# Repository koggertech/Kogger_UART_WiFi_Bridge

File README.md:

# Kogger Wi‑Fi Bridge

Firmware for a small ESP32‑C3‑MINI‑1U board that puts serial devices on Wi‑Fi.

- **Frame‑aware UART ↔ Wi‑Fi relay.** Two UART lines, each mapped to its own UDP port or TCP client.
  Traffic travels as whole protocol frames (Kogger SBP KP1/KP2, u‑blox UBX, MAVLink 1/2) packed into
  datagrams of at most 512 bytes. Anything else passes through as raw bytes, in order.
- **Kogger SBP device** (board ID 87) **on either port.** A host that speaks Kogger SBP uses X1 or X2, in either
  role, to configure Wi‑Fi, the relay and the network, to read state and statistics, and to update the firmware;
  everything except firmware updates also works over the network. The module answers discovery (`ID_VERSION` to
  address 0), so KoggerApp finds it without knowing its address, and it reports what it sees on each port: the rates,
  whether a host or devices sit there, the devices heard, the traffic by protocol. The update exchange is
  the one KoggerApp uses for Kogger devices; its file dialog needs `*.ufww` added ([docs/UPDATE.md](docs/UPDATE.md)).
  The Wi‑Fi settings need a host that implements the `ID_WIFI` / `ID_WIFI_NET` contract
  ([docs/SBP_WIFI.md](docs/SBP_WIFI.md)); `host/sbpframe.py` has Python helpers for the frame and for
  most payloads (state, scan, saved networks, radio, role, access point, addresses, lines, clients).
- **Station or access point.** As a station the module joins an existing network: up to 8 saved networks,
  auto‑connect to the strongest one. As an access point it runs its own network with a DHCP server for up
  to 10 clients.
- **IP bridge (optional).** IPv4 packets over SLIP on the serial link, NAT into Wi‑Fi. This is for a Linux
  host without a Wi‑Fi adapter; the daemon is in `host/`.
- **Safe updates.** Two firmware slots, the image is checked before the switch, and an image that does not
  prove itself is rolled back automatically.
- **GODIO boat telemetry.** Line 1 can listen to the controller wire of a GODIO boat and pass on its position,
  heading and supply voltage as MAVLink ([docs/GODIO_F9.md](docs/GODIO_F9.md)).
- **Reproducible build.** The same sources and ESP‑IDF give the same image byte for byte, so a release
  file can be checked by building its tag.

## Example application

HeadUnit is a boat display computer, a Linux board that talks Kogger SBP to the boat's equipment. It has no usable
Wi‑Fi of its own, so the module sits on one of its UARTs at 3 Mbaud and joins the boat's access point. The equipment
on the boat sends Kogger SBP, MAVLink and UBX; the module relays this traffic between the head unit and the boat over
UDP. On the same port the module answers its own SBP address 87 and sends its Wi‑Fi state reports.

In the access‑point role the same board can be the boat‑side end: it bridges a sonar or autopilot
UART to phones and laptops on its own network.

## Key figures (firmware 0.23.0)

| | |
|---|---|
| Module | ESP32‑C3‑MINI‑1U (RISC‑V, 160 MHz, 4 MB flash, U.FL antenna connector) |
| Board | 20 × 30 mm, 4 layers; two JST GH 4‑pin connectors; supply 4.5–24 V on X1 (3.3 V / 1 A step‑down module) |
| Wi‑Fi | 802.11 b/g/n, 2.4 GHz, 20/40 MHz; Espressif LR mode optional; TX power 2–20 dBm in 11 steps |
| Roles | station (default) or access point (open, WPA2, WPA2/WPA3; channels 1–11; up to 10 clients) |
| Serial lines | X1 = UART0, X2 = UART1, equal for control and relay; 9600–5 000 000 baud, 8N1, set for each port; default 921600 on both |
| Relay | per line: off, UDP (fixed peer, last ≤ 4 senders, or broadcast) or TCP client; frames up to 4096 B |
| Control | Kogger SBP: `ID_WIFI` 0x57, `ID_WIFI_NET` 0x58, `ID_WIFI_SURVEY` 0x59, `ID_WIFI_RF` 0x5A, `ID_WIFI_PROFILE` 0x5B and the common device IDs, from any line or the network |
| Antenna swap | the radio switched off over SBP until a timer (needed when asked over the network, up to 600 s), an "on" request or a reboot (0.20) |
| Status LED | lit steadily without a link, a 100 ms flash every 2.1 s with one (0.20) |
| Profiles | every saved setting loaded as one profile: checked whole, saved at once, then a reboot into it; the module reports the profile's name and whether a setting changed since (0.22) |
| Line 1 translator | GODIO F9 telemetry → MAVLink 2 (position, heading, voltage, satellites), listen‑only; a setting (0.21), in this repository's build from 0.23 |
| Update | over SBP, from a wire or (since 0.17) the network; A/B slots of 1.875 MiB; SHA‑256 check; confirmation after 60 s, rollback at 180 s |
| Factory settings | station knowing the network `KoggerBridge` (build options `WB_FACTORY_SSID` / `WB_FACTORY_PASS`), lines relaying to 10.0.0.10:14444 / 14445; BOOT held 5 s resets the port rates, 10 s every setting |
| Image size | 0.97 MB, 49 % of a slot (0.23.0, UART build); reproducible: no build date, time or path in it |
| Serial throughput | baud / 10 bytes per second each way: 92 KB/s at 921600, 200 KB/s at 2 Mbaud |

The serial line, not Wi‑Fi, is the bottleneck at these rates. Measured figures, test conditions and charts
are in the [datasheet](docs/KoggerWiFi_datasheet.pdf) and in [docs/DESIGN.md](docs/DESIGN.md).

## Documentation

| Document | Contents |
|---|---|
| [docs/HARDWARE.md](docs/HARDWARE.md) | board, connectors, power, wiring, flashing without auto‑reset |
| [docs/FLASHER.md](docs/FLASHER.md) | Windows flasher: firmware into a module in the bootloader, one window, no tools to install |
| [hardware/](hardware/) | KiCad project of the board, schematic PDF, Gerbers, BOM, pick‑and‑place |
| [docs/SBP_WIFI.md](docs/SBP_WIFI.md) | Kogger SBP contract: frame, common IDs, `ID_WIFI` 0x57, `ID_WIFI_NET` 0x58, `ID_WIFI_SURVEY` 0x59, `ID_WIFI_RF` 0x5A, `ID_WIFI_PROFILE` 0x5B |
| [docs/NETWORK.md](docs/NETWORK.md) | station / access point, AP settings, address and DHCP, UART lines and their ports |
| [docs/RELAY.md](docs/RELAY.md) | frame‑aware relay: framing, packing, buffers, back‑pressure, statistics |
| [docs/UPDATE.md](docs/UPDATE.md) | firmware update over SBP: procedure, safety argument, test log |
| [docs/GODIO_F9.md](docs/GODIO_F9.md) | line 1 on a GODIO boat's telemetry wire: wiring, F9 frames, the MAVLink sent, the boat's profile |
| [docs/PROTOCOL.md](docs/PROTOCOL.md) | IP bridge: SLIP framing, text commands, host daemon |
| [docs/PARAMETERS.md](docs/PARAMETERS.md) | every setting with default and range, build options, timing constants, buffers |
| [docs/DESIGN.md](docs/DESIGN.md) | architecture, tasks, memory, ESP‑IDF pitfalls, measurements, open issues |
| [docs/BUILD_AND_TEST.md](docs/BUILD_AND_TEST.md) | build, flash, PC tests, bench tools, host install |
| [docs/KoggerWiFi_datasheet.pdf](docs/KoggerWiFi_datasheet.pdf) | datasheet: summary, parameters and charts |
| [SECURITY.md](SECURITY.md) | security model and what to change before deployment |
| [CHANGELOG.md](CHANGELOG.md) | release history and verification status |

## Repository layout

| Directory | Contents |
|---|---|
| `firmware/` | ESP‑IDF project (C) |
| `host/` | Linux daemon for the IP bridge, CLI client, udev/systemd/NetworkManager files; Python mirrors of the wire formats |
| `tests/` | PC tests: the Python mirrors against the firmware's portable C, compiled on the PC, byte for byte |
| `tools/` | bench tools: flashing, SBP/relay/ping checks, update and packaging, charts and datasheet; `gps_sniffer/`, an identifier of unknown serial lines |
| `profiles/` | module profiles for `tools/profile.py`: a GODIO boat |
| `hardware/` | KiCad 10 project of the reference board and its fabrication outputs |
| `docs/` | documentation, charts, datasheet |
| `LICENSES/` | license notices of included third‑party material (MAVLink generated code) |

## Quick start

Just to put the firmware on a board: download `KoggerWiFiFlasher_EN.exe` and `KoggerWiFi_X.Y.Z.ufww` from the
[releases](https://github.com/koggertech/Kogger_UART_WiFi_Bridge/releases) and follow [docs/FLASHER.md](docs/FLASHER.md).

To build:

```
python tests/test_all.py                       # PC tests, no hardware: "... checks, 0 failed"
python tests/test_f9.py                        # the GODIO F9 translator, the same way
cd firmware
idf.py -B build-uart -D SDKCONFIG=build-uart/sdkconfig -D "SDKCONFIG_DEFAULTS=sdkconfig.defaults;sdkconfig.defaults.uart" build
```

Flashing, the native‑USB variant and the bench checks are described in
[docs/BUILD_AND_TEST.md](docs/BUILD_AND_TEST.md). Tested with ESP‑IDF v5.5.5.

## Status

- **Verified on hardware (0.1–0.18):**
  - SBP device checks;
  - baud rates 9600 to 2 Mbaud on a bench adapter, 2/3/4 Mbaud on a head unit's UART;
  - IP bridge through NAT;
  - station auto‑connect;
  - firmware update, recovery from a lost chunk, a corrupted image refused;
  - relay to a boat network over UDP;
  - 0.11.0 installed on a head unit's module over SBP at 3 Mbaud (7/7 checks), all settings kept;
  - 0.12.0 on a bench module: the port rules (29/29 checks in both roles), the SBP device checks (38/38);
  - 0.12.0 on the head unit's module (7/7); a sonar on the access point's X2 seen on the head unit over an LR‑only
    module‑to‑module link;
  - 0.13.0 on a bench module: both BOOT resets (5 s: only the port rates; 10 s: factory settings), the factory station
    lines, a module set up under an earlier firmware keeping its X2 rate and access point after the update, both ports
    accepting 5 000 000 baud;
  - 0.13.0 and 0.14.0 on the head unit's module (7/7 each), every saved setting read before and compared after
    (`tools/module_state.py`);
  - 0.14.0: 60 requests at once all answered (58 on 0.13), a mixed burst of ten request types answered in full;
  - 0.15.0: a port rate set through that very port saved at once and kept across a reboot; the BOOT 5 s press
    restoring 921600 on both ports with every other setting kept;
  - 0.16.0: a channel survey in the station role - 11 channels swept, the pages, the flags and the refusals
    (`tools/bench_survey.py`), with the Wi-Fi link back afterwards;
  - 0.18.0: the first firmware update over the air - an access-point module updated through a head unit's relay
    (7/7, every setting kept); the link rate on both ends of a b/g/n link, 11n MCS7 with short guard interval both
    ways (`tools/bench_linkrate.py`); an image that could not be confirmed over a busy LR link rolled back to the
    previous one at the next power-on;
  - 0.19.0: both modules updated, one over its UART and one over the air (7/7 each, every setting kept); the LR
    rate field calibrated by frame timing: code 0x1A is 500 kbit/s (bound 372-380 kbit/s in 6 of 6 windows).
- **Not yet verified on hardware:** the timing bound's control on 802.11n frames (none were timed: they came
  aggregated); the channel survey in the access-point role; data at 5 Mbaud (the bench adapter stops at 2 Mbaud); the kept station lines of a
  module updated from 0.12; two factory modules relaying to each other; the 0.11 transmit fix under a saturated 921600 port; an abandoned transfer; a host on X2; the native USB variant; the IP bridge daemon on a Linux host; LR range and throughput over distance.

The status of each release is in [CHANGELOG.md](CHANGELOG.md).

## License

MIT, © 2026 KOGGER LLC, <https://kogger.tech>. See [LICENSE](LICENSE). Third‑party notices: [THIRD_PARTY.md](THIRD_PARTY.md).

The KOGGER logo on the bottom silkscreen of the board is not licensed under the MIT License. The fab zip in
`hardware/outputs` includes it: before making boards that KOGGER LLC does not supply, delete the logo from B.SilkS
and regenerate the outputs with `tools/make_hw_outputs.py`.

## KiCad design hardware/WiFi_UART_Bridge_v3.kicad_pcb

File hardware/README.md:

# Hardware: Wi‑Fi UART bridge board v3

KiCad 10 project of the reference board, the board that was manufactured and is in use. Every drill hole
and every solder‑paste opening of this board matches the fabrication files the board was made from (checked, see
below).

| File | Contents |
|---|---|
| `WiFi_UART_Bridge_v3.kicad_pro` | project (open this in KiCad 10 or later) |
| `WiFi_UART_Bridge_v3.kicad_sch` | schematic, one A4 sheet |
| `WiFi_UART_Bridge_v3.kicad_pcb` | board: 20 × 30 mm, 4 layers |
| `WiFi_UART_Bridge.kicad_sym`, `WiFi_UART_Bridge.pretty/` | project symbol and footprint libraries (`sym-lib-table`, `fp-lib-table`) |
| `3d/` | plain box bodies for renders (module, switch, 4 A diodes); other parts use KiCad library models |
| `outputs/WiFi_UART_Bridge_v3_schematic.pdf` | schematic |
| `outputs/WiFi_UART_Bridge_v3_fab.zip` | Gerbers, Excellon drill, drill map, Gerber job file, pick‑and‑place, BOM |
| `outputs/WiFi_UART_Bridge_v3_bom.csv`, `_pos.csv` | BOM and pick‑and‑place (top side, mm, origin at the lower‑left board corner) |

The outputs are generated by `python tools/make_hw_outputs.py` (needs `kicad-cli` of KiCad 10).

## Board

| | |
|---|---|
| Size | 20 × 30 mm, a 2 mm wide, 4 mm deep notch with a rounded end between the two connectors |
| PCB | 4 layers, FR4 1.2 mm, 18 µm copper, ENIG finish, green solder mask, white silkscreen |
| Stackup in the file | nominal: 0.2 mm prepreg, 0.708 mm core, 0.2 mm prepreg; use the fab's standard 1.2 mm 4‑layer stackup |
| Layers | F.Cu: signals and GND pour; In1.Cu: GND; In2.Cu: VCC, +3.3 V and UART routing plus a GND pour; B.Cu: GND pour and the test pads |
| Design rules | track 0.2 mm min, clearance 0.2 mm, vias 0.7/0.3 mm (82), copper to edge 0.25 mm |
| Components | 37 on the top side; 4 test pads on the bottom |

## Circuit

- **Module U1:** ESP32‑C3‑MINI‑1U with a U.FL connector for an external 2.4 GHz antenna. The EN pin has a 10 kΩ
  pull‑up and 1 µF to GND (power‑on delay). The strapping pins GPIO2, GPIO8 and GPIO9 have 10 kΩ pull‑ups.
  The BOOT button SB1 pulls GPIO9 low.
- **Power:**
  - VCC arrives on X1 pin 4 through the Schottky diode D9 (SDM4A40EP3, reverse‑polarity protection).
  - The step‑down module U2 (TI LMZM23601V3: 4–36 V in, 3.3 V out, up to 1 A per TI) makes +3.3 V.
  - VCC range: 4.5–24 V (rated; not measured on a board). The lower limit is the regulator's 4 V plus the diode
    drop; the upper limit stays below the 25 V rating of the input capacitors C5/C6.
- **X2 pin 4 (VCC_X2):** two 0 Ω links. R8 connects it to VCC. R9 + D8 feed it from +3.3 V through a Schottky
  diode. Both links are fitted in the BOM, so X2 pin 4 carries VCC; with R8 left out it carries about 3 V. Through R8
  the board can also be powered from X2 pin 4, without the reverse‑polarity diode.
- **UART protection:** each line has a series resistor on the connector side, 150 Ω on TX and 1 kΩ on RX. On the
  module side, Schottky diodes (BAS3005B‑02V) clamp each line to GND and to a clamp rail 3.3S. D1 feeds that rail from
  +3.3 V; the 3.3 V Zener D12 and C4 absorb the clamp current, so over‑voltage on a connector does not pump up +3.3 V.
- **LED VD1:** GPIO0 → 1 kΩ → green LED → GND, lit when GPIO0 is high. Since 0.20 the firmware shows the link on it
  ([docs/HARDWARE.md](../docs/HARDWARE.md)).
- **Test pads on the bottom (1.6 mm):** TP1 DM (GPIO18, USB D−), TP2 DP (GPIO19, USB D+), TP3 TX and TP4 RX of line 1
  (GPIO5/GPIO4). The USB pads allow flashing through the C3's USB Serial/JTAG.

| Connector | Pin 1 | Pin 2 | Pin 3 | Pin 4 |
|---|---|---|---|---|
| X1 (line 0) | TX (GPIO21) | RX (GPIO20) | GND | VCC in (through D9) |
| X2 (line 1) | TX (GPIO5) | RX (GPIO4) | GND | VCC_X2 |

X1 and X2 are JST GH 4‑pin headers, 1.25 mm, right angle (SM04B‑GHS‑TB). The mating housing is GHR‑04V‑S.
The bottom silkscreen names the pins.

## How the KiCad project was checked

1. **Board:**
   - footprints in one project library with plain names;
   - courtyards on U1, U2, X1, X2 and SB1 and fab outlines on U2, X1, X2 and SB1; the passives, diodes and LED have
     silkscreen outlines only, the test pads none (the board's DRC does not require courtyards);
   - footprints linked to their schematic symbols by UUID;
   - KiCad library 3D models, aligned by fitting the library footprint's pads onto these pads (residual ≤ 0.1 mm),
     plus three plain boxes;
   - stackup 1.2 mm, 18 µm copper, ENIG, green solder mask, white silkscreen;
   - drill/place origin at the lower‑left corner.
2. **Connectivity:** the schematic netlist and the board partition all 134 pins into the same 32 nets. The only board
   pads without a symbol pin are 14 unconnected NC pads of U1.
3. **Against the fabrication files of the manufactured board:**
   - all 82 drill holes match (≤ 0.0005 mm);
   - all 152 top and 4 bottom solder‑paste openings match in position (≤ 0.0004 mm) and size;
   - in the original pick‑and‑place file 33 of 37 parts match exactly. For D8, D9, X1 and X2 that file gives a body
     centre instead of the footprint origin; their pads are among the matched paste openings.
4. **ERC:** clean. **DRC with schematic parity:** no parity errors, no unconnected items, no clearance errors.
   Remaining items are inherited from the original layout:
   - 1 error: C3 pad 2 has a single thermal spoke into the top GND pour after the zones are refilled;
   - 26 warnings: silkscreen text 0.7 mm high, below KiCad's default minimum of 0.8 mm;
   - 3 warnings: silkscreen over copper.

Changes to the content of the original design, all visible in the files:
- The four bottom test pads were free pads in the original layout. They are now test points TP1–TP4 in the schematic
  and on the board, excluded from the BOM and the pick‑and‑place.
- PWR_FLAG symbols and a "Power flags for ERC" block were added, as KiCad's ERC requires. U2's DNC and PGOOD pins got
  no‑connect marks.
- Part data come from the production BOM: value, manufacturer part number, manufacturer. Fields of the original part
  database (stock, storage location, local datasheet paths, distributor links) were not carried over.
- The original schematic's database item for D1, D3, D4, D6, D7, D10, D11, D13, D14 was SDM05A30CP3‑7. The production
  BOM and the footprint (SC‑79) use BAS3005B‑02VH6327, and so does this project.
- ERC ignores "off grid" in this project: the ESP32 module symbol has its pins on a 2.5 mm pitch.
- The board's copper‑to‑edge constraint is 0.25 mm: the layout keeps connector mounting pads (at 0.25 mm), stitching
  vias and a few tracks 0.25–0.48 mm from the edge.
- Solder mask: green in this project; the first production run of board v3 used blue.
- A duplicate set of connector labels outside the board outline on the front silkscreen was removed.

## License

The hardware design files are published under the same MIT license as the rest of the repository
([../LICENSE](../LICENSE)). KiCad library symbols embedded in the schematic, the symbol `VCC_X2` of the project library
(derived from KiCad `power:VCC`) and the KiCad 3D models the board refers to are covered by the KiCad libraries'
license ([../THIRD_PARTY.md](../THIRD_PARTY.md)).

The KOGGER logo on the bottom silkscreen of the board is not licensed under the MIT License. The fab zip in
`hardware/outputs` includes it: before making boards that KOGGER LLC does not supply, delete the logo from B.SilkS
and regenerate the outputs with `tools/make_hw_outputs.py`.

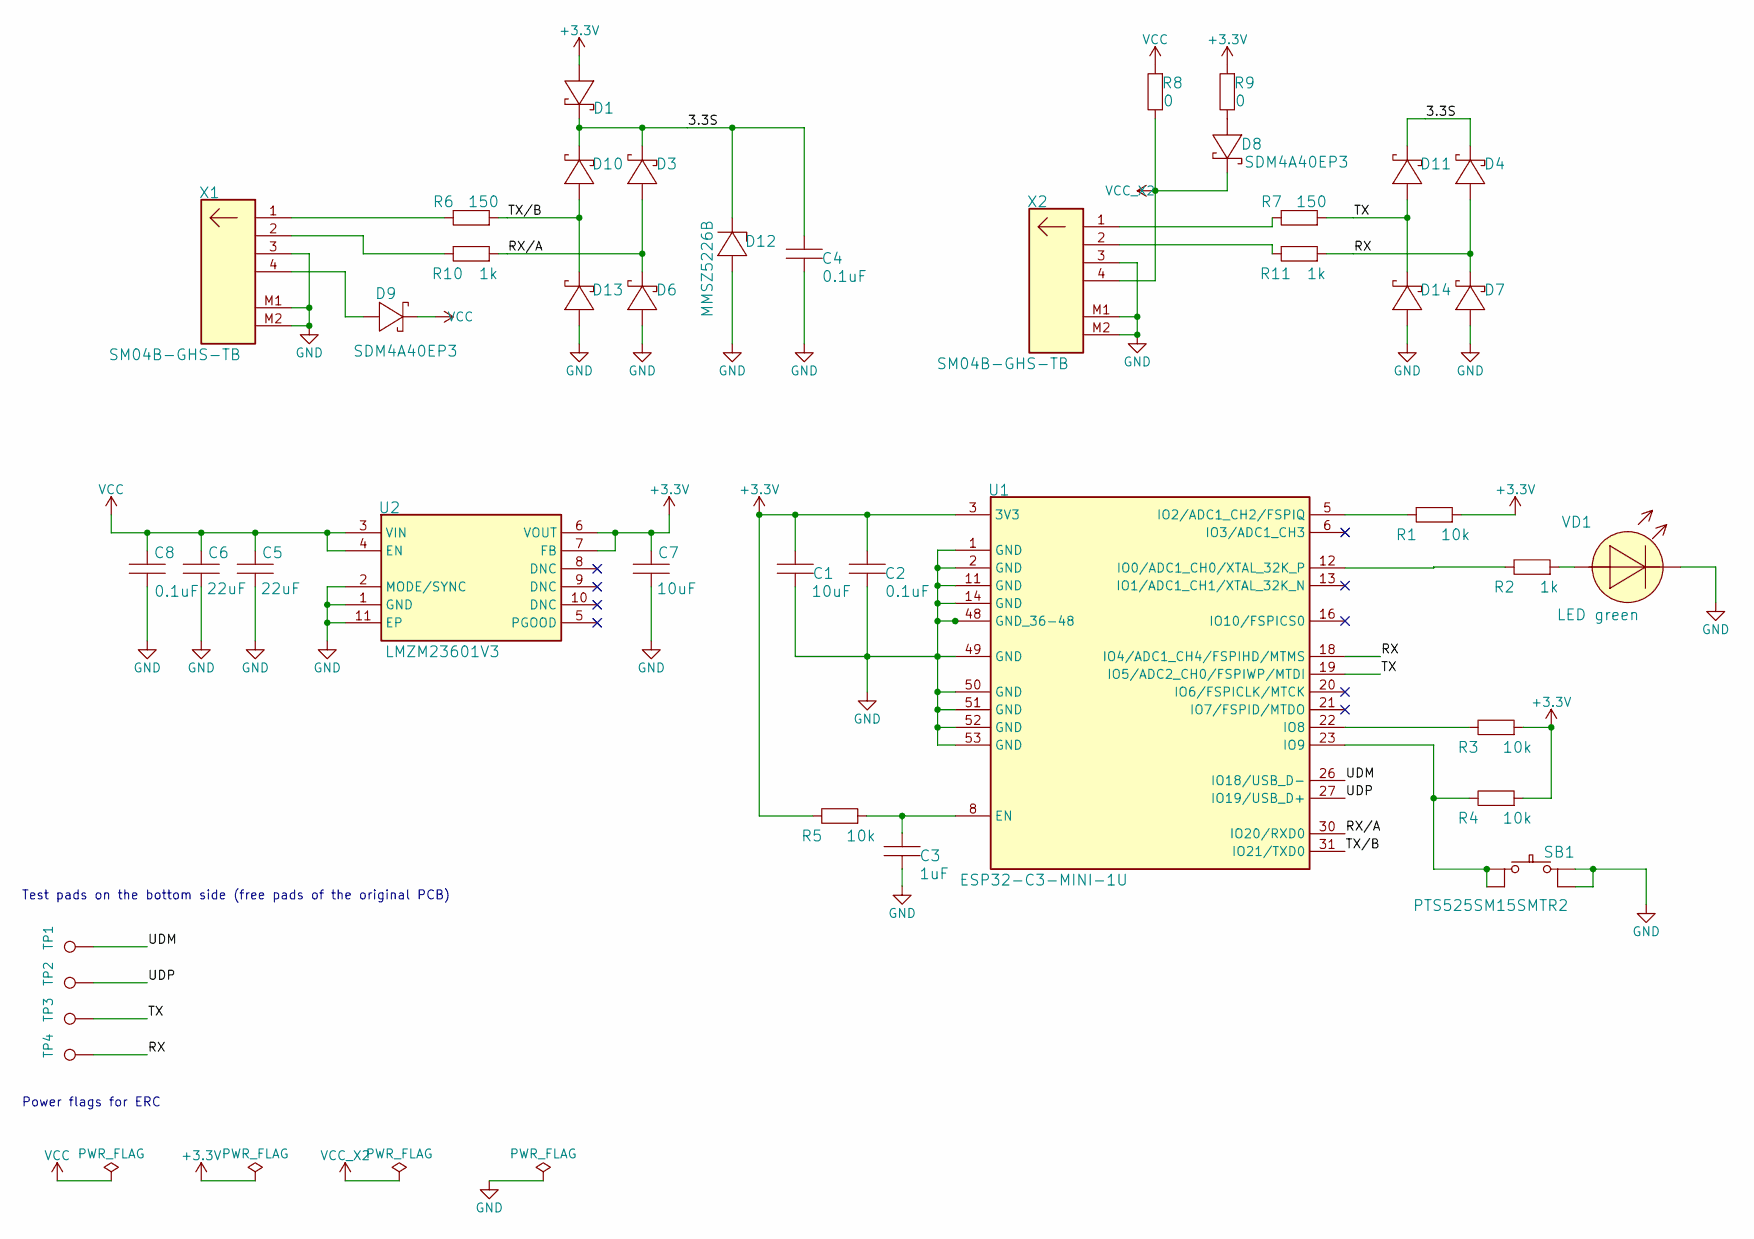
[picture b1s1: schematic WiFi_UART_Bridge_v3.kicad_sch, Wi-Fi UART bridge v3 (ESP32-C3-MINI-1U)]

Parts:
C1, C7: 10uF; C_0603_1608Metric_Big; MPN CL10A106MO8NQNC
C2, C4, C8: 0.1uF; C_0603_1608Metric_Big; MPN CL10B104JB8NNNC
C3: 1uF; C_0603_1608Metric_Big; MPN CL10A105KB8NNNC
C5, C6: 22uF; C_0805_2012Metric; MPN CL21A226MAYNNNE
D1, D3, D4, D6, D7, D10, D11, D13, D14: BAS3005B-02V; D_SC-79; MPN BAS3005B-02VH6327
D8, D9: SDM4A40EP3; D_SDM4A40EP3; MPN SDM4A40EP3-7B
D12: MMSZ5226B; D_SOD-123; MPN SZMMSZ5226BT1G
R1, R3, R4, R5: 10k; R_0603_1608Metric_Big; MPN ERJ-3EKF1002V
R2, R10, R11: 1k; R_0603_1608Metric_Big; MPN ERJ-3EKF1001V
R6, R7: 150; R_0603_1608Metric_Big; MPN ERJ-3EKF1500V
R8, R9: 0; R_0603_1608Metric_Big; MPN ERJ-3GEY0R00V
SB1: PTS525SM15SMTR2; SW_CK_PTS525SM15SMTR2; MPN PTS525SM15SMTR2 LFS
TP1: DM; TestPoint_Pad_D1.6mm
TP2: DP; TestPoint_Pad_D1.6mm
TP3: TX; TestPoint_Pad_D1.6mm
TP4: RX; TestPoint_Pad_D1.6mm
U1: ESP32-C3-MINI-1U; MPN ESP32-C3-MINI-1U
U2: LMZM23601V3; TI_SIL0010A_LMZM2360x; MPN LMZM23601V3SILR
VD1: LED green; LED_0603_1608Metric; MPN FYLS-0603UGC
X1, X2: SM04B-GHS-TB; JST_GH_SM04B-GHS-TB_1x04-1MP_P1.25mm_Horizontal; MPN SM04B-GHS-TB(LF)(SN)

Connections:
+3.3V: C1.1, C2.1, C7.2, D1.2 (A), R1.1, R3.1, R4.1, R5.2, R9.1, U1.3 (3V3), U2.6 (VOUT), U2.7 (FB)
/3.3S: C4.1, D1.1 (C), D3.1 (C), D4.1 (C), D10.1 (C), D11.1 (C), D12.1 (C)
/RX: D4.2 (A), D7.1 (C), R11.1, TP4.1, U1.18 (IO4/ADC1_CH4/FSPIHD/MTMS)
/RX/A: D3.2 (A), D6.1 (C), R10.1, U1.30 (IO20/RXD0)
/TX: D11.2 (A), D14.1 (C), R7.1, TP3.1, U1.19 (IO5/ADC2_CH0/FSPIWP/MTDI)
/TX/B: D10.2 (A), D13.1 (C), R6.1, U1.31 (IO21/TXD0)
/UDM: TP1.1, U1.26 (IO18/USB_D-)
/UDP: TP2.1, U1.27 (IO19/USB_D+)
GND: C1.2, C2.2, C3.2, C4.2, C5.1, C6.1, C7.1, C8.2, D6.2 (A), D7.2 (A), D12.2 (A), D13.2 (A), D14.2 (A), SB1.3, SB1.4, U1.1 (GND), U1.2 (GND), U1.11 (GND), U1.14 (GND), U1.36 (GND), U1.37 (GND), U1.38 (GND), U1.39 (GND), U1.40 (GND), U1.41 (GND), U1.42 (GND), U1.43 (GND), U1.44 (GND), U1.45 (GND), U1.46 (GND), U1.47 (GND), U1.48 (GND_36-48), U1.49 (GND), U1.50 (GND), U1.51 (GND), U1.52 (GND), U1.53 (GND), U2.1 (GND), U2.2 (MODE/SYNC), U2.11 (EP), VD1.2, X1.3, X1.M1, X1.M2, X2.3, X2.M1, X2.M2
unnamed: D8.2 (A), R9.2
unnamed: D9.2 (A), X1.4
unnamed: R2.1, VD1.1
unnamed: R6.2, X1.1
unnamed: R7.2, X2.1
unnamed: R10.2, X1.2
unnamed: R11.2, X2.2
unnamed: C3.1, R5.1, U1.8 (EN)
unnamed: R2.2, U1.12 (IO0/ADC1_CH0/XTAL_32K_P)
unnamed: R1.2, U1.5 (IO2/ADC1_CH2/FSPIQ)
unnamed: R3.2, U1.22 (IO8)
unnamed: R4.2, SB1.1, SB1.2, U1.23 (IO9)
VCC: C5.2, C6.2, C8.1, D9.1 (C), R8.1, U2.3 (VIN), U2.4 (EN)
VCC_X2: D8.1 (C), R8.2, X2.4

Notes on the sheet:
Test pads on the bottom side (free pads of the original PCB)
Power flags for ERC

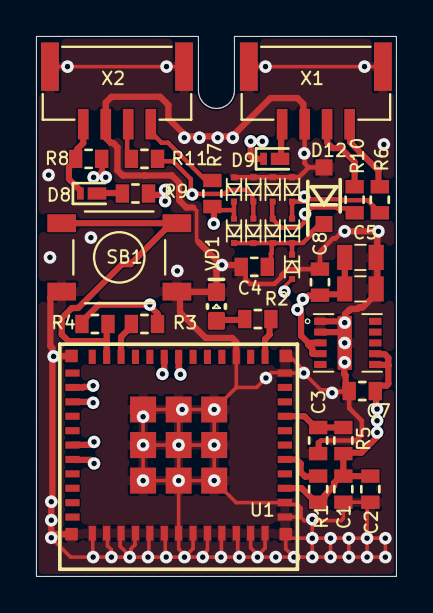
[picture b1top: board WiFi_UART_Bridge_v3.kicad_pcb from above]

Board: 4 copper layers, 20.0 x 30.0 mm, 41 parts (0 on the bottom side), 23 nets.

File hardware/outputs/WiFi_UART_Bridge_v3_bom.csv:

"References","Value","Footprint","MPN","Manufacturer","Description","Qty"
"C1,C7","10uF","WiFi_UART_Bridge:C_0603_1608Metric_Big","CL10A106MO8NQNC","Samsung Electro-Mechanics","Capacitor, ceramic, 0603","2"
"C2,C4,C8","0.1uF","WiFi_UART_Bridge:C_0603_1608Metric_Big","CL10B104JB8NNNC","Samsung Electro-Mechanics","Capacitor, ceramic, 0603","3"
"C3","1uF","WiFi_UART_Bridge:C_0603_1608Metric_Big","CL10A105KB8NNNC","Samsung Electro-Mechanics","Capacitor, ceramic, 0603","1"
"C5,C6","22uF","WiFi_UART_Bridge:C_0805_2012Metric","CL21A226MAYNNNE","Samsung Electro-Mechanics","Capacitor, ceramic, 0805","2"
"D1,D3,D4,D6,D7,D10,D11,D13,D14","BAS3005B-02V","WiFi_UART_Bridge:D_SC-79","BAS3005B-02VH6327","Infineon Technologies","Schottky diode 30 V 0.5 A, SC-79","9"
"D8,D9","SDM4A40EP3","WiFi_UART_Bridge:D_SDM4A40EP3","SDM4A40EP3-7B","Diodes Incorporated","Schottky diode 40 V 4 A","2"
"D12","MMSZ5226B","WiFi_UART_Bridge:D_SOD-123","SZMMSZ5226BT1G","onsemi","Zener diode 3.3 V 500 mW, SOD-123","1"
"R1,R3,R4,R5","10k","WiFi_UART_Bridge:R_0603_1608Metric_Big","ERJ-3EKF1002V","Panasonic","Resistor 1 %, 0603","4"
"R2,R10,R11","1k","WiFi_UART_Bridge:R_0603_1608Metric_Big","ERJ-3EKF1001V","Panasonic","Resistor 1 %, 0603","3"
"R6,R7","150","WiFi_UART_Bridge:R_0603_1608Metric_Big","ERJ-3EKF1500V","Panasonic","Resistor 1 %, 0603","2"
"R8,R9","0","WiFi_UART_Bridge:R_0603_1608Metric_Big","ERJ-3GEY0R00V","Panasonic","Jumper 0 Ohm, 0603","2"
"SB1","PTS525SM15SMTR2","WiFi_UART_Bridge:SW_CK_PTS525SM15SMTR2","PTS525SM15SMTR2 LFS","C&K","Tactile switch SPST-NO (BOOT)","1"
"U1","ESP32-C3-MINI-1U","WiFi_UART_Bridge:ESP32-C3-MINI-1U","ESP32-C3-MINI-1U","Espressif Systems","Wi-Fi / Bluetooth LE module, ESP32-C3, 4 MB flash, U.FL antenna connector","1"
"U2","LMZM23601V3","WiFi_UART_Bridge:TI_SIL0010A_LMZM2360x","LMZM23601V3SILR","Texas Instruments","Step-down power module, 3.3 V 1 A","1"
"VD1","LED green","WiFi_UART_Bridge:LED_0603_1608Metric","FYLS-0603UGC","","LED green, 0603","1"
"X1,X2","SM04B-GHS-TB","WiFi_UART_Bridge:JST_GH_SM04B-GHS-TB_1x04-1MP_P1.25mm_Horizontal","SM04B-GHS-TB(LF)(SN)","JST","JST GH header 4 pins, 1.25 mm, right angle, SMD","2"
